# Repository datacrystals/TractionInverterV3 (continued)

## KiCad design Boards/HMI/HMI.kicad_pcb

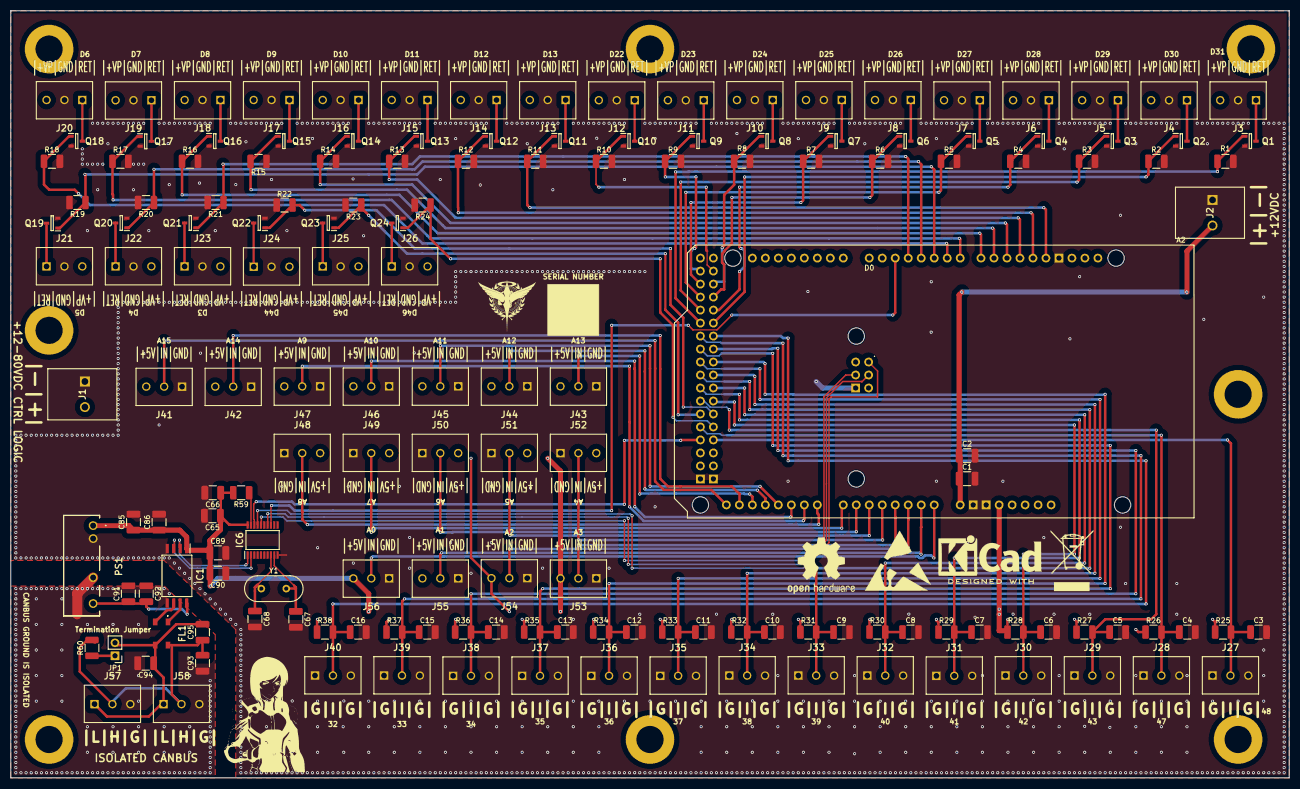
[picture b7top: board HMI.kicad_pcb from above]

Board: 4 copper layers, 250.0 x 150.0 mm, 166 parts (1 on the bottom side), 99 nets.

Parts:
A2: Arduino_Mega2560_R3_Shield
C1, C66, C86, C90, C91: 1uF; C_1210_3225Metric_Pad1.33x2.70mm_HandSolder
C2, C3, C4, C5, C6, C7, C8, C9, C10, C11, C12, C13, C14, C15, C16, C65, C85, C89, C92: 100nF; C_1210_3225Metric_Pad1.33x2.70mm_HandSolder
C67, C68, C93, C94, C95: 22pF; C_1210_3225Metric_Pad1.33x2.70mm_HandSolder
FL1: ACT45B-101-2P-TL003; ACT45B1012PTL003
H1, H2, H3, H4, H5, H6, H7, H8: MountingHole_Pad; MountingHole_5.3mm_M5_ISO7380_Pad
IC1: ISO1042BDWVR; SOIC127P1150X280-8N
IC6: MCP2515-e_ST; SOP65P640X120-20N
J1, J2: 1987724
J3, J4, J5, J6, J7, J8, J9, J10, J11, J12, J13, J14, J15, J16, J17, J18, J19, J20, J21, J22, J23, J24, J25, J26, J27, J28, J29, J30, J31, J32, J33, J34, J35, J36, J37, J38, J39, J40, J41, J42, J43, J44, J45, J46, J47, J48, J49, J50, J51, J52, J53, J54, J55, J56, J57, J58: 5442251
JP1: Jumper_2_Open; PinHeader_1x02_P2.54mm_Vertical
PS1: RFMM-0505S; RFMM0505S
Q1, Q2, Q3, Q4, Q5, Q6, Q7, Q8, Q9, Q10, Q11, Q12, Q13, Q14, Q15, Q16, Q17, Q18, Q19, Q20, Q21, Q22, Q23, Q24: SSM3K361R,LF; SOT95P240X88-3N
R1, R2, R3, R4, R5, R6, R7, R8, R9, R10, R11, R12, R13, R14, R15, R16, R17, R18, R19, R20, R21, R22, R23, R24, R25, R26, R27, R28, R29, R30, R31, R32, R33, R34, R35, R36, R37, R38, R59: 4.7k; R_1210_3225Metric_Pad1.30x2.65mm_HandSolder
R60: 120; R_1210_3225Metric_Pad1.30x2.65mm_HandSolder
Y1: 8MHz; Crystal_HC49-4H_Vertical

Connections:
+5V: A2.5V1 (5V), C65.1, C66.1, C85.1, C86.1, C89.1, C90.2, IC1.1 (VCC1), IC6.20 (VDD), J41.3, J42.3, J43.3, J44.3, J45.3, J46.3, J47.3, J48.3, J49.3, J50.3, J51.3, J52.3, J53.3, J54.3, J55.3, J56.3, PS1.1 (+VIN), R25.1, R26.1, R27.1, R28.1, R29.1, R30.1, R31.1, R32.1, R33.1, R34.1, R35.1, R36.1, R37.1, R38.1, R59.2
+12V: A2.VIN, C1.1, C2.1, J2.2
+V_PanelLogic: J1.2, J3.3, J4.3, J5.3, J6.3, J7.3, J8.3, J9.3, J10.3, J11.3, J12.3, J13.3, J14.3, J15.3, J16.3, J17.3, J18.3, J19.3, J20.3, J21.3, J22.3, J23.3, J24.3, J25.3, J26.3
A0_IN: A2.A0, J56.2
A1_IN: A2.A1, J55.2
A2_IN: A2.A2, J54.2
A3_IN: A2.A3, J53.2
A4_IN: A2.A4, J52.2
A5_IN: A2.A5, J51.2
A6_IN: A2.A6, J50.2
A7_IN: A2.A7, J49.2
A8_IN: A2.A8, J48.2
A9_IN: A2.A9, J47.2
A10_IN: A2.A10, J46.2
A11_IN: A2.A11, J45.2
A12_IN: A2.A12, J44.2
A13_IN: A2.A13, J43.2
A14_IN: A2.A14, J42.2
A15_IN: A2.A15, J41.2
CANBUS_ISO_5V: C91.1, C92.2, IC1.8 (VCC2), PS1.7 (+VOUT)
CANBUS_ISO_GND: C91.2, C92.1, C93.1, C94.2, IC1.5 (GND2), J57.3, J58.3, PS1.5 (-VOUT)
CAN_CS: A2.D49, IC6.18 (~CS)
CAN_INT: A2.D2 (D2_INT0), IC6.13 (~INT)
CAN_SCK: A2.SCK (SPI_SCK), IC6.14 (SCK)
CAN_SI: A2.MOSI (SPI_MOSI), IC6.16 (SI)
CAN_SO: A2.MISO (SPI_MISO), IC6.17 (SO)
CanH_External: C93.2, C95.1, FL1.4, J57.2, J58.2, R60.2
CanL_External: C94.1, C95.2, FL1.3, J57.1, J58.1, JP1.2 (B)
D3_OUT: A2.D3 (D3_INT1), Q21.1 (G), R21.1
D3_PWR: J23.1, Q21.3 (D)
D4_OUT: A2.D4, Q20.1 (G), R20.1
D4_PWR: J22.1, Q20.3 (D)
D5_OUT: A2.D5, Q19.1 (G), R19.1
D5_PWR: J21.1, Q19.3 (D)
D6_OUT: A2.D6, Q18.1 (G), R18.1
D6_PWR: J20.1, Q18.3 (D)
D7_OUT: A2.D7, Q17.1 (G), R17.1
D7_PWR: J19.1, Q17.3 (D)
D8_OUT: A2.D8, Q16.1 (G), R16.1
D8_PWR: J18.1, Q16.3 (D)
D9_OUT: A2.D9, Q15.1 (G), R15.1
D9_PWR: J17.1, Q15.3 (D)
D10_OUT: A2.D10, Q14.1 (G), R14.1
D10_PWR: J16.1, Q14.3 (D)
D11_OUT: A2.D11, Q13.1 (G), R13.1
D11_PWR: J15.1, Q13.3 (D)
D12_OUT: A2.D12, Q12.1 (G), R12.1
D12_PWR: J14.1, Q12.3 (D)
D13_OUT: A2.D13, Q11.1 (G), R11.1
D13_PWR: J13.1, Q11.3 (D)
D22_OUT: A2.D22, Q10.1 (G), R10.1
D22_PWR: J12.1, Q10.3 (D)
D23_OUT: A2.D23, Q9.1 (G), R9.1
D23_PWR: J11.1, Q9.3 (D)
D24_OUT: A2.D24, Q8.1 (G), R8.1
D24_PWR: J10.1, Q8.3 (D)
D25_OUT: A2.D25, Q7.1 (G), R7.1
D25_PWR: J9.1, Q7.3 (D)
D26_OUT: A2.D26, Q6.1 (G), R6.1
D26_PWR: J8.1, Q6.3 (D)
D27_OUT: A2.D27, Q5.1 (G), R5.1
D27_PWR: J7.1, Q5.3 (D)
D28_OUT: A2.D28, Q4.1 (G), R4.1
D28_PWR: J6.1, Q4.3 (D)
D29_OUT: A2.D29, Q3.1 (G), R3.1
D29_PWR: J5.1, Q3.3 (D)
D30_OUT: A2.D30, Q2.1 (G), R2.1
D30_PWR: J4.1, Q2.3 (D)
D31_OUT: A2.D31, Q1.1 (G), R1.1
D31_PWR: J3.1, Q1.3 (D)
D32_IN: A2.D32, C16.1, J40.2, R38.2
D33_IN: A2.D33, C15.1, J39.2, R37.2
D34_IN: A2.D34, C14.1, J38.2, R36.2
D35_IN: A2.D35, C13.1, J37.2, R35.2
D36_IN: A2.D36, C12.1, J36.2, R34.2
D37_IN: A2.D37, C11.1, J35.2, R33.2
D38_IN: A2.D38, C10.1, J34.2, R32.2
D39_IN: A2.D39, C9.1, J33.2, R31.2
D40_IN: A2.D40, C8.1, J32.2, R30.2
D41_IN: A2.D41, C7.1, J31.2, R29.2
D42_IN: A2.D42, C6.1, J30.2, R28.2
D43_IN: A2.D43, C5.1, J29.2, R27.2
D44_OUT: A2.D44, Q22.1 (G), R22.1
D44_PWR: J24.1, Q22.3 (D)
D45_OUT: A2.D45, Q23.1 (G), R23.1
D45_PWR: J25.1, Q23.3 (D)
D46_OUT: A2.D46, Q24.1 (G), R24.1
D46_PWR: J26.1, Q24.3 (D)
D47_IN: A2.D47, C4.1, J28.2, R26.2
D48_IN: A2.D48, C3.1, J27.2, R25.2
GND: A2.GND1 (GND), A2.GND2 (GND), A2.GND3 (GND), A2.GND4 (SPI_GND), A2.GND5 (GND), A2.GND6 (GND), C1.2, C2.2, C3.2, C4.2, C5.2, C6.2, C7.2, C8.2, C9.2, C10.2, C11.2, C12.2, C13.2, C14.2, C15.2, C16.2, C65.2, C66.2, C67.2, C68.2, C85.2, C86.2, C89.2, C90.1, IC1.4 (GND1), IC6.10 (VSS), J1.1, J2.1, J3.2, J4.2, J5.2, J6.2, J7.2, J8.2, J9.2, J10.2, J11.2, J12.2, J13.2, J14.2, J15.2, J16.2, J17.2, J18.2, J19.2, J20.2, J21.2, J22.2, J23.2, J24.2, J25.2, J26.2, J27.1, J27.3, J28.1, J28.3, J29.1, J29.3, J30.1, J30.3, J31.1, J31.3, J32.1, J32.3, J33.1, J33.3, J34.1, J34.3, J35.1, J35.3, J36.1, J36.3, J37.1, J37.3, J38.1, J38.3, J39.1, J39.3, J40.1, J40.3, J41.1, J42.1, J43.1, J44.1, J45.1, J46.1, J47.1, J48.1, J49.1, J50.1, J51.1, J52.1, J53.1, J54.1, J55.1, J56.1, PS1.2 (-VIN), Q1.2 (S), Q2.2 (S), Q3.2 (S), Q4.2 (S), Q5.2 (S), Q6.2 (S), Q7.2 (S), Q8.2 (S), Q9.2 (S), Q10.2 (S), Q11.2 (S), Q12.2 (S), Q13.2 (S), Q14.2 (S), Q15.2 (S), Q16.2 (S), Q17.2 (S), Q18.2 (S), Q19.2 (S), Q20.2 (S), Q21.2 (S), Q22.2 (S), Q23.2 (S), Q24.2 (S), R1.2, R2.2, R3.2, R4.2, R5.2, R6.2, R7.2, R8.2, R9.2, R10.2, R11.2, R12.2, R13.2, R14.2, R15.2, R16.2, R17.2, R18.2, R19.2, R20.2, R21.2, R22.2, R23.2, R24.2
unnamed: FL1.1, IC1.7 (CANH)
unnamed: FL1.2, IC1.6 (CANL)
unnamed: IC1.3 (RXD), IC6.2 (RXCAN)
unnamed: IC1.2 (TXD), IC6.1 (TXCAN)
unnamed: C67.1, IC6.9 (OSC1), Y1.2
unnamed: C68.1, IC6.8 (OSC2), Y1.1
unnamed: IC6.19 (~RESET), R59.1
unnamed: JP1.1 (A), R60.1

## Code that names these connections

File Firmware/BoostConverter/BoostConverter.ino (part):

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#define LED_INDICATOR2_PIN 8  // Output Enabled Indicator
#define LED_INDICATOR3_PIN 9  // Temperature OK
#define FAN_TACH 3            // Fan Tachometer
#define FAN_PWM 5             // Fan PWM duty cycle control
#define OUTPUT_ENABLE_PIN 7   // Pin which enables output, must be high for output to be on
#define PHASE_1_TEMP_SENSOR_PIN A4 // Phase A Temp Sensor
#define PHASE_2_TEMP_SENSOR_PIN A5 // Phase A Temp Sensor
#define CAN_INT_PIN 2         // Pin for canbus interrupt
#define CAN_CS_PIN 10         // Pin for canbus chip select
#define CAN_SI_PIN 11         // Pin for canbus signal in
#define CAN_SO_PIN 12         // Pin for canbus signal out
#define CAN_SCK_PIN 13        // Pin for canbus clock

#define DEVICE_ID 0x01 // Set this to a unique value (0x00 to 0x3F)

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FaultManager faultManager;

#define CAN_ID DEVICE_ID
#define CAN_CS_PIN 10
#define CAN_INT_PIN 2

CANBusManager canBus(CAN_ID, CAN_CS_PIN, CAN_INT_PIN);


bool OutputEnabled = false; // Indicates if the output has been enabled or not
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
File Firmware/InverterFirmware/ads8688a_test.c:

#include "pico/stdlib.h"
#include "hardware/spi.h"
#include <stdio.h>

// === PIN DEFINITIONS ===
#define PIN_SPI_SCK     10  // GPIO10
#define PIN_SPI_MOSI    11  // GPIO11
#define PIN_SPI_MISO    12  // GPIO12
#define PIN_SPI_CS      9   // GPIO9

// === SPI SETTINGS ===
#define SPI_PORT spi0
#define SPI_BAUDRATE 1 * 1000 * 1000  // 1 MHz

// === ADS8688A CHANNEL SELECT COMMANDS ===
#define CMD_MAN_CH0 0xC000
#define CMD_MAN_CH1 0xC400
#define CMD_MAN_CH2 0xC800
#define CMD_MAN_CH3 0xCC00
#define CMD_MAN_CH4 0xD000
#define CMD_MAN_CH5 0xD400
#define CMD_MAN_CH6 0xD800
#define CMD_MAN_CH7 0xDC00

// === FUNCTION DECLARATIONS ===
void ads8688a_init();
void ads8688a_send_command(uint16_t command, uint8_t *rx_buf);
uint16_t ads8688a_read_channel(uint16_t command);
void ads8688a_read_all_channels();

// === GLOBALS ===
const uint16_t channel_cmds[8] = {
    CMD_MAN_CH0, CMD_MAN_CH1, CMD_MAN_CH2, CMD_MAN_CH3,
    CMD_MAN_CH4, CMD_MAN_CH5, CMD_MAN_CH6, CMD_MAN_CH7
};

const char *channel_labels[8] = {
    "AIN_0P (pin 16)", "AIN_1P (pin 18)", "AIN_2P (pin 21)", "AIN_3P (pin 23)",
    "AIN_4P (pin 25)", "AIN_5P (pin 27)", "AIN_6P (pin 12)", "AIN_7P (pin 14)"
};

// === FUNCTION IMPLEMENTATIONS ===
void ads8688a_init() {
    spi_init(SPI_PORT, SPI_BAUDRATE);
    gpio_set_function(PIN_SPI_SCK, GPIO_FUNC_SPI);
    gpio_set_function(PIN_SPI_MOSI, GPIO_FUNC_SPI);
    gpio_set_function(PIN_SPI_MISO, GPIO_FUNC_SPI);

    gpio_init(PIN_SPI_CS);
    gpio_set_dir(PIN_SPI_CS, GPIO_OUT);
    gpio_put(PIN_SPI_CS, 1); // Deselect chip
}

void ads8688a_send_command(uint16_t command, uint8_t *rx_buf) {
    uint8_t tx_buf[2] = { (command >> 8) & 0xFF, command & 0xFF };
    gpio_put(PIN_SPI_CS, 0);
    spi_write_read_blocking(SPI_PORT, tx_buf, rx_buf, 2);
    gpio_put(PIN_SPI_CS, 1);
}

uint16_t ads8688a_read_channel(uint16_t command) {
    uint8_t rx_buf[2];
    ads8688a_send_command(command, rx_buf);
    return ((uint16_t)rx_buf[0] << 8) | rx_buf[1];
}

void ads8688a_read_all_channels() {
    printf("Reading ADS8688A Channels:\n");
    for (int i = 0; i < 8; ++i) {
        uint16_t value = ads8688a_read_channel(channel_cmds[i]);
        printf("  Channel %d [%s] = %u\n", i, channel_labels[i], value);
    }
    printf("\n");
}

// === MAIN ===
int main() {
    stdio_init_all();
    sleep_ms(1000);  // Wait for USB serial to come up

    printf("ADS8688A SPI Test\n");

    ads8688a_init();

    while (true) {
        ads8688a_read_all_channels();
        sleep_ms(1000);
    }

    return 0;
}

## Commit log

2025-02-12 Update boost converter, add inverter
2025-02-20 Finish Boost Converter
2025-02-20 Update boost converter layout
2025-02-22 update stl
2025-02-22 udpate
2025-03-06 Add BoostConverter Software
2025-03-07 Implement fault handler, temp sense, voltage monitor, enable output, blink codes
2025-03-08 Implement canbus
2025-03-08 basic canbus working
2025-03-16 Update DC Link Bus VRM Control Firmware
2025-03-16 Update Schematic
2025-03-22 add dynamic brake schematic
2025-03-22 mechanical for dynamic brake grid
2025-03-27 Update boost converter, add dynamic brake grid, etc
2025-03-27 update canbus driver test
2025-03-30 Update Canbus protocol for vrm
2025-04-15 Dynamic Brake Grid FW V0
2025-04-16 Update Schematics, Inverter, Gate Driver, Mechanical, Software
2025-04-17 Polling for DyBrk over CAN
2025-04-22 ashley push
2025-04-22 vsense
2025-04-22 finish vsense
2025-04-23 asdad
2025-04-23 Attempted to use canopen functions
2025-04-23 floundering
2025-04-24 Added example project of using CAN.
2025-04-24 Added CAN Example Project
2025-04-24 chmod scripts
2025-04-24 Update Inverter CAD File
2025-04-24 fix dbgrid
2025-04-24 Inital work on implimenting new CAN system.
2025-04-26 added firmware folder.
2025-04-26 Fix compile bugs
2025-04-26 Made the CAN chip be enabld.
2025-04-26 Added string handler to most code.
2025-04-26 Fixed class variable
2025-04-26 change baud rate
2025-04-26 fix cs pins
2025-04-26 Hardware updates
2025-04-26 add zener diode to lib
2025-04-26 Reorganize Project
2025-04-26 Fix Library Paths
2025-04-26 Fix Lib Paths
2025-04-26 Random work on CAN system
2025-04-26 Fix 3d Models in Boards
2025-04-26 got everything compiling! wooo!
2025-04-26 Added string callback
2025-04-26 Add Filter Caps To ADC Control Board IC
2025-04-26 Removed old CAN system from Dynamic Break Grid
2025-04-26 Added more helpful CAN Messages.
2025-04-26 Added debug messages.
2025-04-26 Added more chatGPT things
2025-04-26 Removed some chromizones
2025-04-26 Added print for all messages recived.
2025-04-26 insanity
2025-04-26 Made all string be in flash memory
2025-04-26 intcest
2025-04-26 added delay
2025-04-26 Fixed compiler error
2025-04-26 extracted the code better
2025-04-26 Added debug message at end of can
2025-04-26 Added more logs
2025-04-26 replaced switch with if else.
2025-04-26 Add Zeners to Power Board
2025-04-26 Update DYBRK Schematic
2025-04-27 Update Dynamic Brake Board
2025-04-27 Fix Silkscreen on new dynamic brake grid
2025-04-27 Update Gate Resistor
2025-04-27 Finalize DyBrk Rev B
2025-04-27 update inverter
2025-04-27 dynamic brake controller mechanical
2025-04-27 Update Control Board Layout
2025-04-27 Finalize Voltage Sense Board
2025-04-28 Generate Bill of Materials
2025-04-28 Update Gate Driver to use non NDA BS Chip
2025-04-28 Update Layouts
2025-04-28 Update board soldermask
2025-04-29 Finalize Dynamic Brake Control Module Mechanical
2025-04-29 Add Label For Dynamic Brake Grid
2025-04-30 Add Control Stand
2025-04-30 u[date
2025-05-01 Update Mechanical Models
2025-05-01 Added Wheel Hub Cad
2025-05-01 Update Mechanical For Inverter
2025-05-01 Added torque plate to wheel hub
2025-05-02 updated label accuracy
2025-05-05 Finish Inverter Mechanical
2025-05-06 Add Choo-Choo Display Base
2025-05-08 Finalize Boards
2025-05-18 added firmware dir
2025-05-18 pushed ads code
2025-05-18 readded Dynamic Brake Grid Code
2025-05-18 boms
2025-05-19 Update Dybrk FW
2025-05-19 Update Dynamic Brake Firmware
2025-05-21 Added test pico code
2025-05-21 work maybe
2025-05-26 Update Pico FW Build System
2025-05-26 Changed pin definition, added force fault test.
2025-05-26 Fixed git code dupication
2025-05-26 added startup message
2025-05-26 Testing new file
2025-05-26 Rename Stuff
2025-05-26 Update Serial Mon
2025-05-26 Added new test code
2025-05-26 leveling the playing field
    gnu17 (since Xcode 14) plus Clang injects -Werror=implicit-function-declaration when targeting modern macOS SDKs, so might as well enforce it for everyone :3
    its good practice anyway
2025-05-26 since implicit function declaration is now an error, i fix
2025-05-27 Update control board
2025-05-28 Added test code for ads8688a
2025-05-28 Added simple test script for CAN on the raspberry pi pico.
